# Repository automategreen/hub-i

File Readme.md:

Insteon Compatible WiFi Hub
===============
> Open Source Secure WiFi Hub for Insteon Devices
***

The Hub I is designed to provide secure cloud control to your existing Insteon network. We are currently working on prototyping with the Spark Core. The final solutions will use the Spark Photon P1.

## Feedback & Support

Please let us know if you like this concept.  We need your support and encouragement to make the prototype a product. Send us an email, [support@automategreen.com](mailto:support@automategreen.com), or a tweet, [@AutomateGreen](https://twitter.com/AutomateGreen).

## Work In Progress

Link Record DB - The all-link record database is not implement yet.  Linking will not work until this is complete.

## UPDATE - CRC Solved!!!

The Insteon CRC issue has been solved.  Thank you Wieslaw Strugala for your help.  Insteon uses two different CRC methods: one for power line (PL) and one for radio (RF).  Wieslaw has solved the PL CRC and pointed me to Peter Shipley who solved the Insteon RF CRC, <https://github.com/evilpete/insteonrf>.  Many thanks to Peter, Wieslaw, and all the others who helped.

## Insteon Over the Spark Cloud

To improve on the standard Insteon Hub, we've used the awesome [Spark OS](https://www.spark.io/) to extend the PLM interface security to the cloud.  No unencrypted open information here. All messaging pass securely to and from the Spark OS.

### Insteon Message

All Insteon messages are sent as HEX strings.  The HEX strings allow for all Insteon messages to fit within the Spark OS packet restriction.  It also minimizes the logic for the hub.

Because the HEX is cryptic and requires an in-depth knowledge of the Insteon HEX commands, we added support for the hub to our Node.js module, [home-controller](https://github.com/automategreen/home-controller).

### Sending an Insteon Command

All the Insteon commands can be sent using HEX strings.

For example, to turn an Insteon switch on, you send a direct command to turn on the device.

```
$ spark call 0123456789ABCDEFGHI insteon 0262AABBCC0F117F
8
```

- Direct command: 0262
- Device ID: AABBCC
- Flags: 0F
- Action (turn on): 11
- Level (50%): 7F

The light turns on to 50%, and the call returns the number of bytes sent to the PLM. In this case `8`. 

### Receiving an Insteon Event

Now you can control your device, but you want more.  You want notifications in real time of from you devices - no problem.  You can use the Spark OS subscribe to receive Insteon messages from your device.

Here's and example of getting notified of motion detected by a motion sensor.

```
$ spark subscribe insteon 0123456789ABCDEFGHI
Subscribing to "insteon" from 0123456789ABCDEFGHI's stream
Listening to: /v1/devices/0123456789ABCDEFGHI/events/insteon
{"name":"insteon","data":"0250aabbcc000001cf1101","ttl":"60","published_at":"2015-01-12T21:16:48.361Z","coreid":"0123456789ABCDEFGHI"}
```

The data field contains the Insteon message.

- Received command: 0250
- Device ID: AABBCC
- Group: 000001
- Flags: cf
- Action (motion detected): 11

### Insteon Request/Response

If you want to query a device for information, you combine the `call` and `subscribe` together. 

First, make sure you subscribe.

```
spark subscribe insteon 0123456789ABCDEFGHI
Subscribing to "insteon" from 0123456789ABCDEFGHI's stream
Listening to: /v1/devices/0123456789ABCDEFGHI/events/insteon
```

Then, send the request. For example, get the light level.

```
$ spark call 0123456789ABCDEFGHI insteon 0262aabbcc0f1900
2
```

You'll then receive the Insteon response from the subscription.

```
{"name":"insteon","data":"0250aabbccffffff2f01ff","ttl":"60","published_at":"2015-01-12T21:16:48.361Z","coreid":"0123456789ABCDEFGHI"}
```

Light is on at 100%.  

If your want an easier way, you can use [home-controller](https://github.com/automategreen/home-controller).

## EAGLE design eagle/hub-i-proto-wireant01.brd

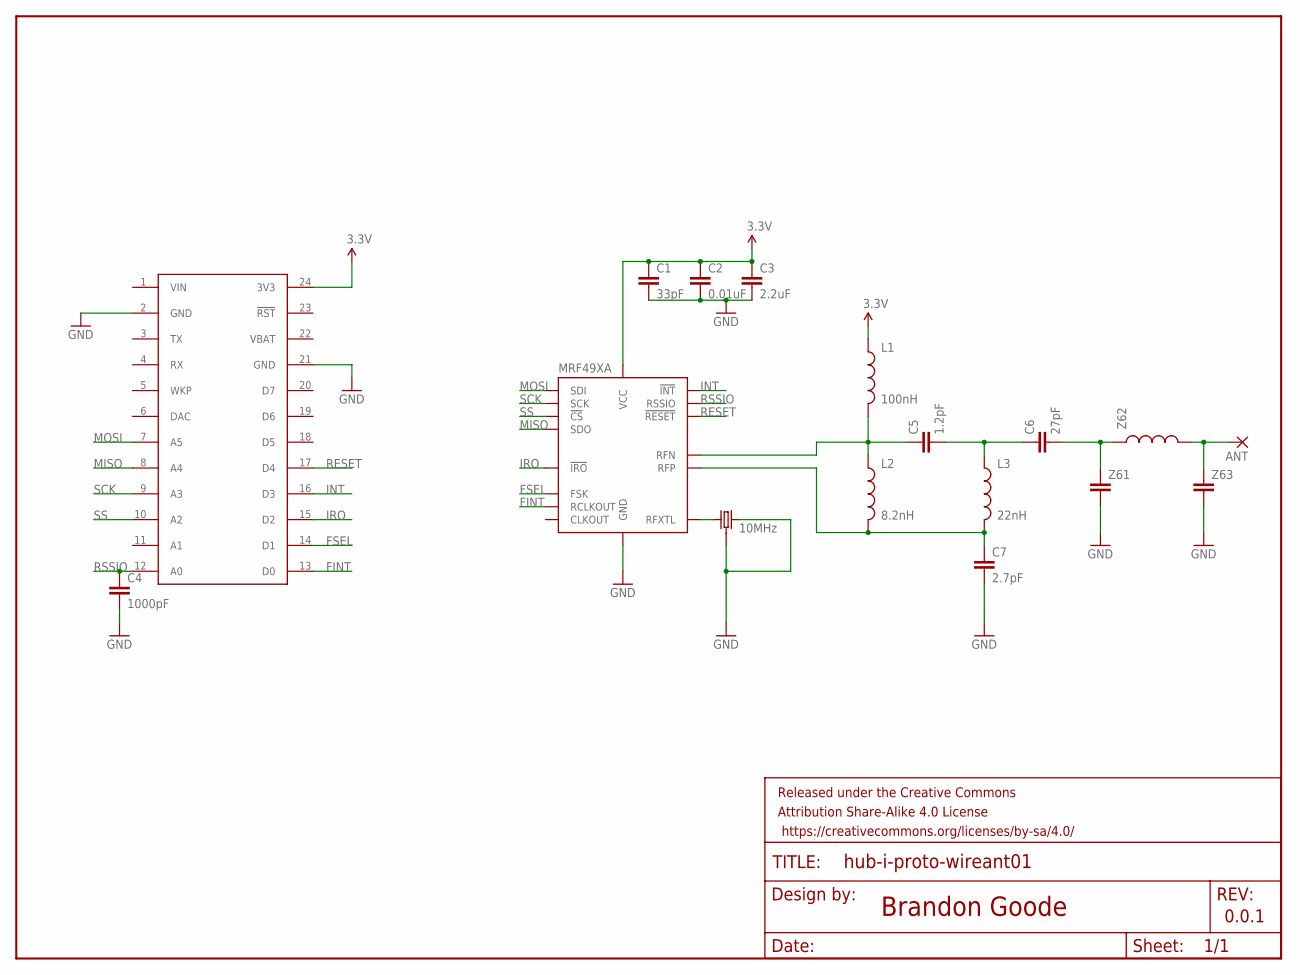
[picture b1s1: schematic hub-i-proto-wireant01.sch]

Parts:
ANT: WIREPAD1,6/0,8; 1,6/0,8
C1: 33pF; 0603-CAP
C2: 0.01uF; 0603-CAP
C3: 2.2uF; 0603-CAP
C4: 1000pF; 0603-CAP
C5: 1.2pF; 0603-CAP
C6: 27pF; 0603-CAP
C7: 2.7pF; 0603-CAP
FRAME1: FRAME-LETTER; CREATIVE_COMMONS
L1: 100nH; 0603
L2: 8.2nH; 0603
L3: 22nH; 0603
MRF49XA: MRF49XATSSOP; TSSOP16
SPARK: SPARK_CORECORE; SPARK_CORE
Y1: 10MHz; CRYSTAL-SMD-5X3
Z61, Z63: CAP0603-CAP; 0603-CAP
Z62: INDUCTOR0603; 0603

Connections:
3.3V: C1.1, C2.1, C3.1, L1.1, MRF49XA.14 (VCC), SPARK.24 (3V3)
ANT: ANT.1, Z62.2, Z63.1
FINT: MRF49XA.7 (RCLKOUT), SPARK.13 (D0)
FSEL: MRF49XA.6 (FSK), SPARK.14 (D1)
GND: C1.2, C2.2, C3.2, C4.2, C7.2, MRF49XA.11 (GND), SPARK.2 (GND), SPARK.21 (GND), Y1.1 (2), Y1.2 (3), Y1.4 (3), Z61.2, Z63.2
INT: MRF49XA.16 (!INT), SPARK.16 (D3)
IRO: MRF49XA.5 (!IRO), SPARK.15 (D2)
MISO: MRF49XA.4 (SDO), SPARK.8 (A4)
MOSI: MRF49XA.1 (SDI), SPARK.7 (A5)
unnamed: C5.2, C6.1, L3.1
unnamed: MRF49XA.9 (RFXTL), Y1.3 (1)
unnamed: C5.1, L1.2, L2.1, MRF49XA.13 (RFN)
unnamed: C7.1, L2.2, L3.2, MRF49XA.12 (RFP)
unnamed: C6.2, Z61.1, Z62.1
RESET: MRF49XA.10 (!RESET), SPARK.17 (D4)
RSSIO: C4.1, MRF49XA.15 (RSSIO), SPARK.12 (A0)
SCK: MRF49XA.2 (SCK), SPARK.9 (A3)
SS: MRF49XA.3 (!CS), SPARK.10 (A2)
VBAT: SPARK.22 (VBAT)
VIN: SPARK.1 (VIN)

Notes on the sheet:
Brandon Goode
0.0.1

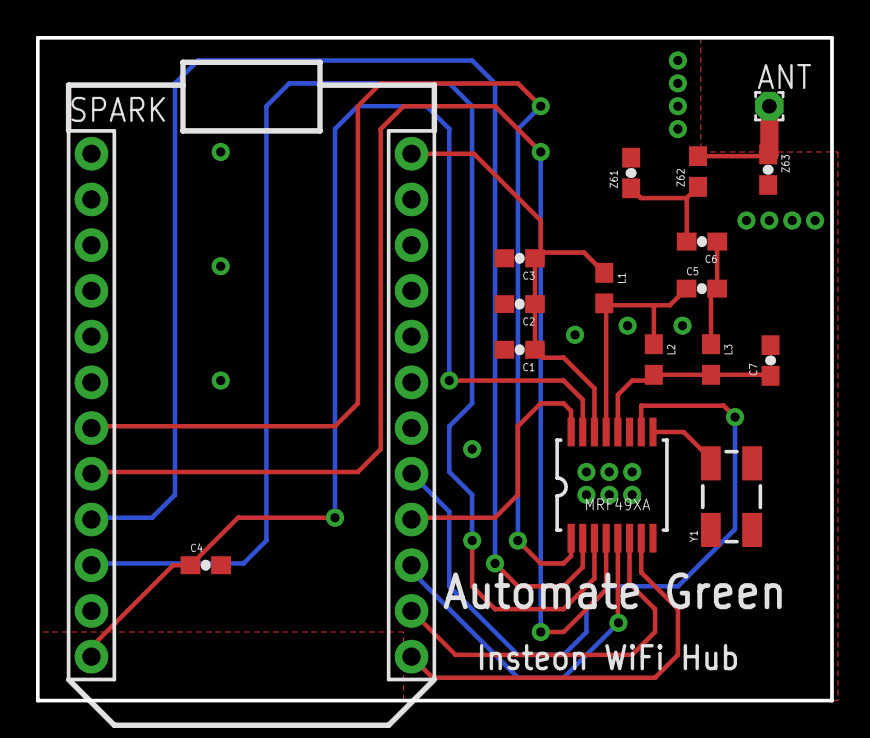
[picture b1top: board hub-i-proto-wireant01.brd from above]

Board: 2 copper layers, 44.1 x 36.8 mm, 18 parts (0 on the bottom side), 18 nets.

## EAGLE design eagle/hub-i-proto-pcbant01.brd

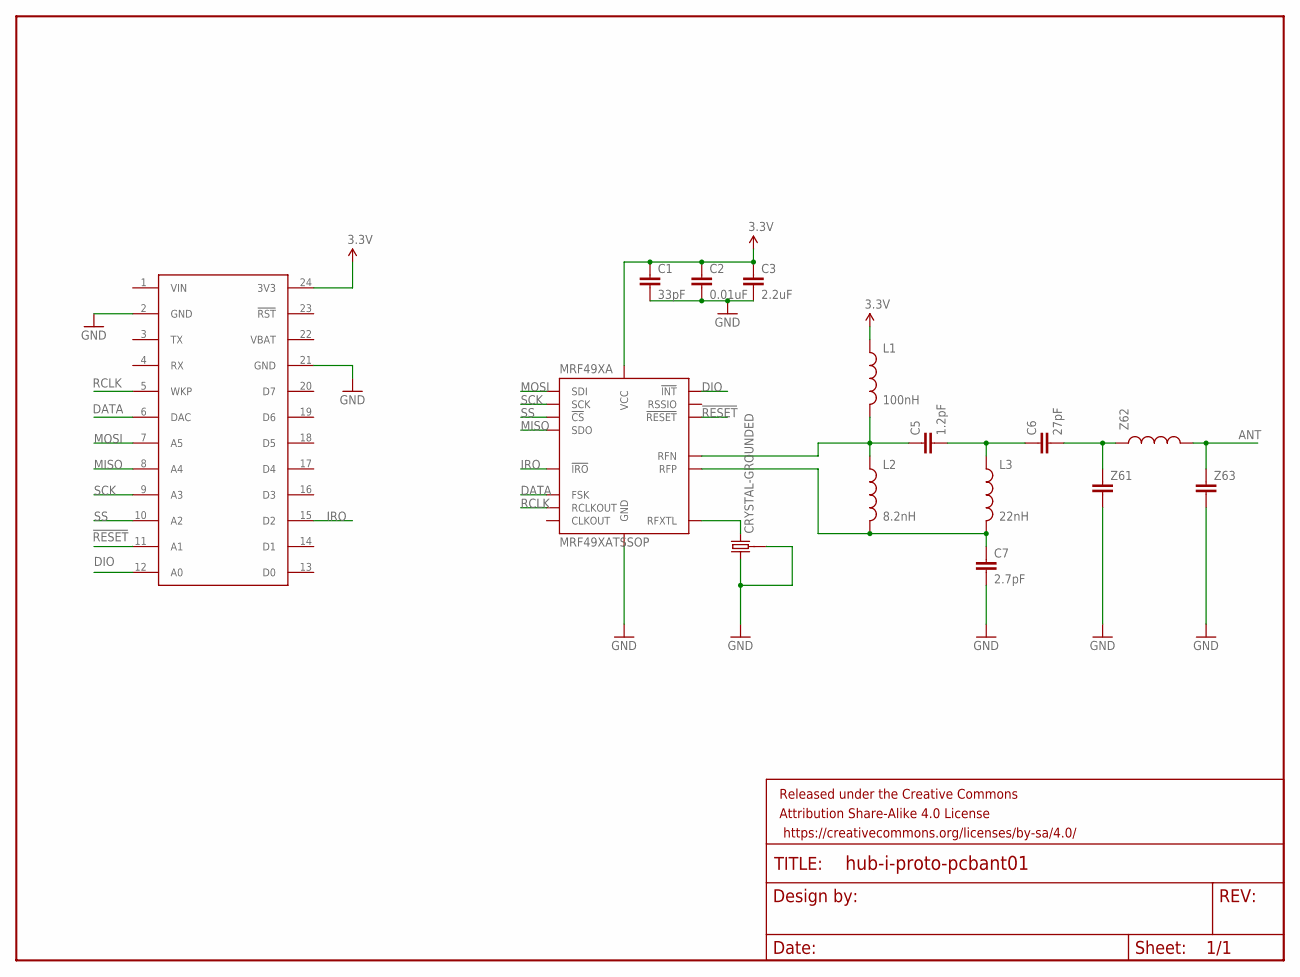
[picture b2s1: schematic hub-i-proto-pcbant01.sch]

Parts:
C1: 33pF; 0603-CAP
C2: 0.01uF; 0603-CAP
C3: 2.2uF; 0603-CAP
C5: 1.2pF; 0603-CAP
C6: 27pF; 0603-CAP
C7: 2.7pF; 0603-CAP
CORE: SPARK_CORECORE; SPARK_CORE
FRAME1: FRAME-LETTER; CREATIVE_COMMONS
L1: 100nH; 0603
L2: 8.2nH; 0603
L3: 22nH; 0603
MRF49XA: MRF49XATSSOP; TSSOP16
Y1: CRYSTAL-GROUNDED; CRYSTAL-SMD-5X3
Z61, Z63: CAP0603-CAP; 0603-CAP
Z62: INDUCTOR0603; 0603

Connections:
3.3V: C1.1, C2.1, C3.1, CORE.24 (3V3), L1.1, MRF49XA.14 (VCC)
!RESET: CORE.11 (A1), MRF49XA.10 (!RESET)
ANT: Z62.2, Z63.1
DATA: CORE.6 (DAC), MRF49XA.6 (FSK)
DIO: CORE.12 (A0), MRF49XA.16 (!INT)
GND: C1.2, C2.2, C3.2, C7.2, CORE.2 (GND), CORE.21 (GND), MRF49XA.11 (GND), Y1.2 (3), Y1.3 (1), Y1.4 (3), Z61.2, Z63.2
IRO: CORE.15 (D2), MRF49XA.5 (!IRO)
MISO: CORE.8 (A4), MRF49XA.4 (SDO)
MOSI: CORE.7 (A5), MRF49XA.1 (SDI)
unnamed: C5.2, C6.1, L3.1
unnamed: MRF49XA.9 (RFXTL), Y1.1 (2)
unnamed: C5.1, L1.2, L2.1, MRF49XA.13 (RFN)
unnamed: C7.1, L2.2, L3.2, MRF49XA.12 (RFP)
unnamed: C6.2, Z61.1, Z62.1
RCLK: CORE.5 (WKP), MRF49XA.7 (RCLKOUT)
SCK: CORE.9 (A3), MRF49XA.2 (SCK)
SS: CORE.10 (A2), MRF49XA.3 (!CS)
VBAT: CORE.22 (VBAT)
VIN: CORE.1 (VIN)

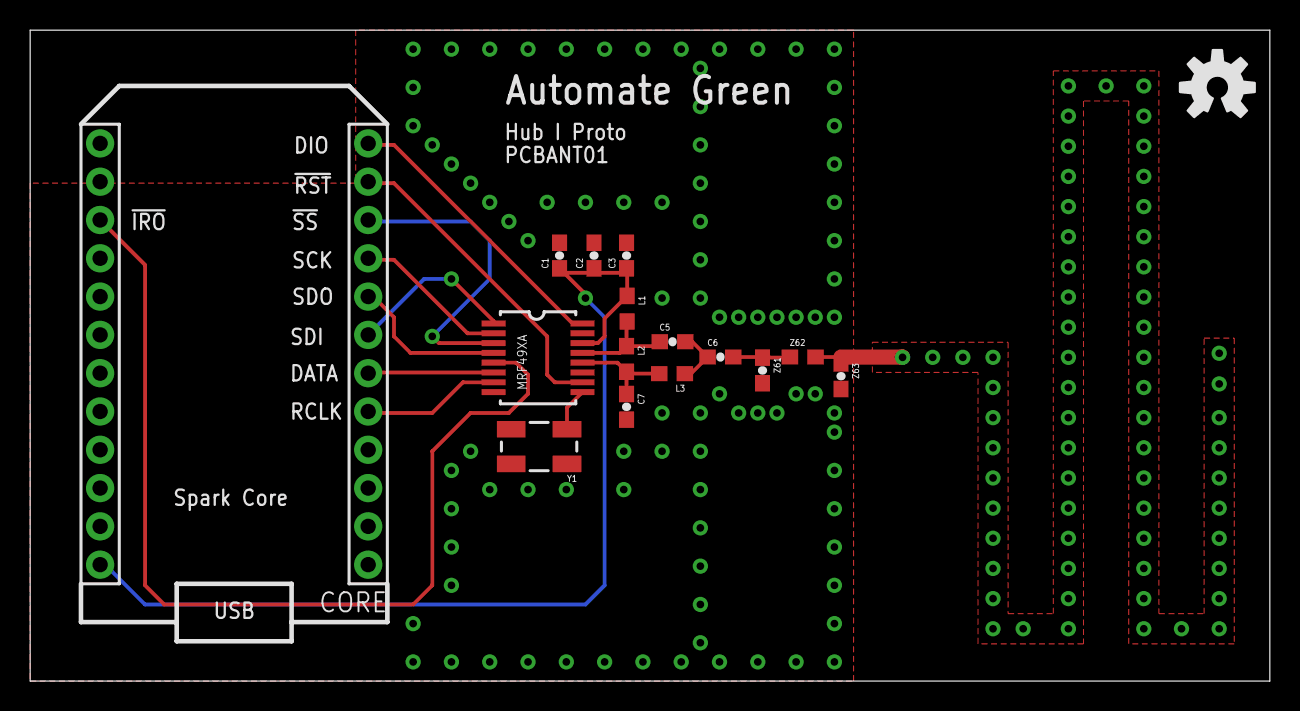
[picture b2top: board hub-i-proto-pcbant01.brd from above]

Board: 2 copper layers, 82.2 x 43.2 mm, 17 parts (0 on the bottom side), 17 nets.

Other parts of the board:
U$2: OSHW-LOGO-M

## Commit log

2016-01-11 crc working and updates for photon

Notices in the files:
parts and their libraries:
SparkFun-Passives: Licensing: Creative Commons ShareAlike 4.0 International - https://creativecommons.org/licenses/by-sa/4.0
SparkFun-Aesthetics: Released under the Creative Commons Attribution Share-Alike 4.0 License
SparkFun-Aesthetics: https://creativecommons.org/licenses/by-sa/4.0
